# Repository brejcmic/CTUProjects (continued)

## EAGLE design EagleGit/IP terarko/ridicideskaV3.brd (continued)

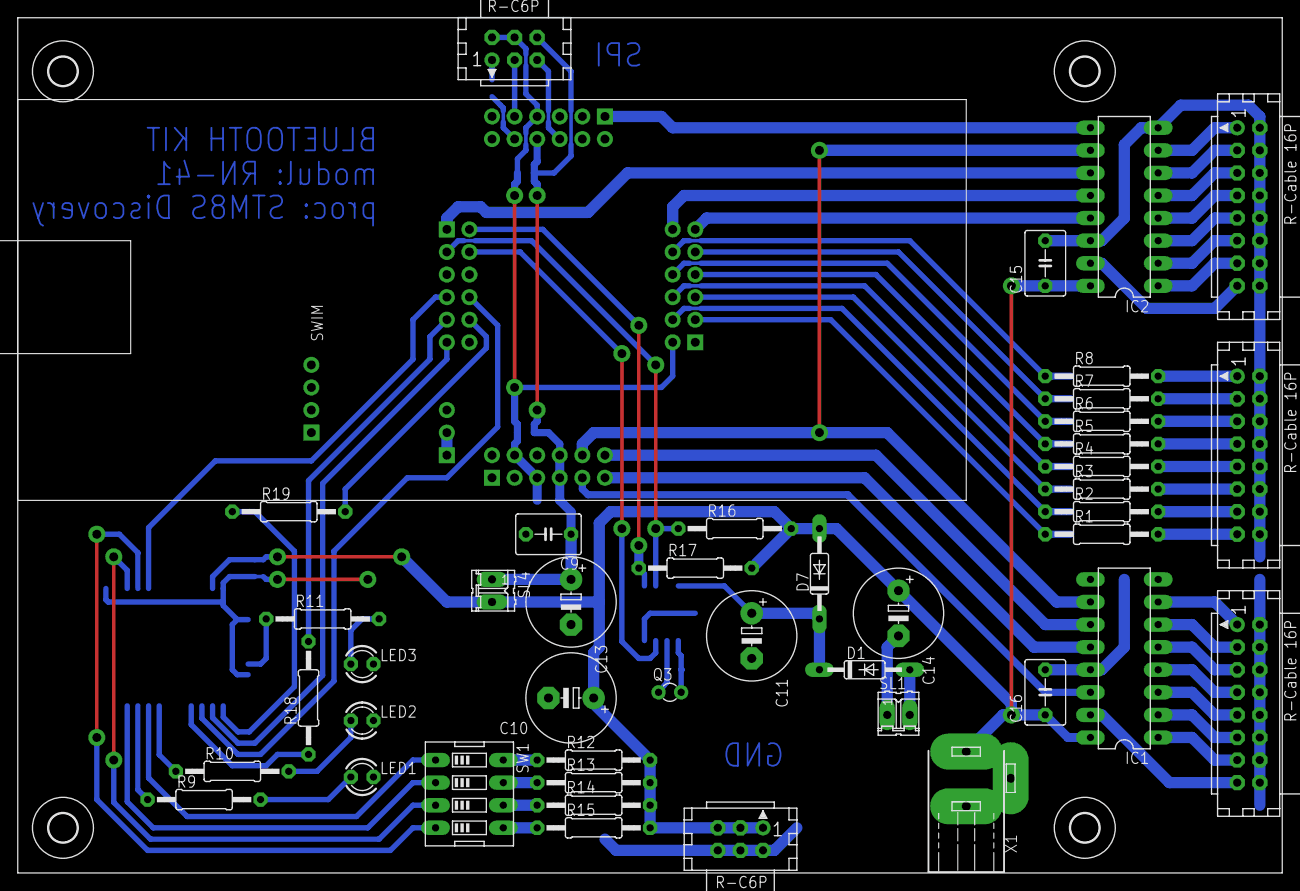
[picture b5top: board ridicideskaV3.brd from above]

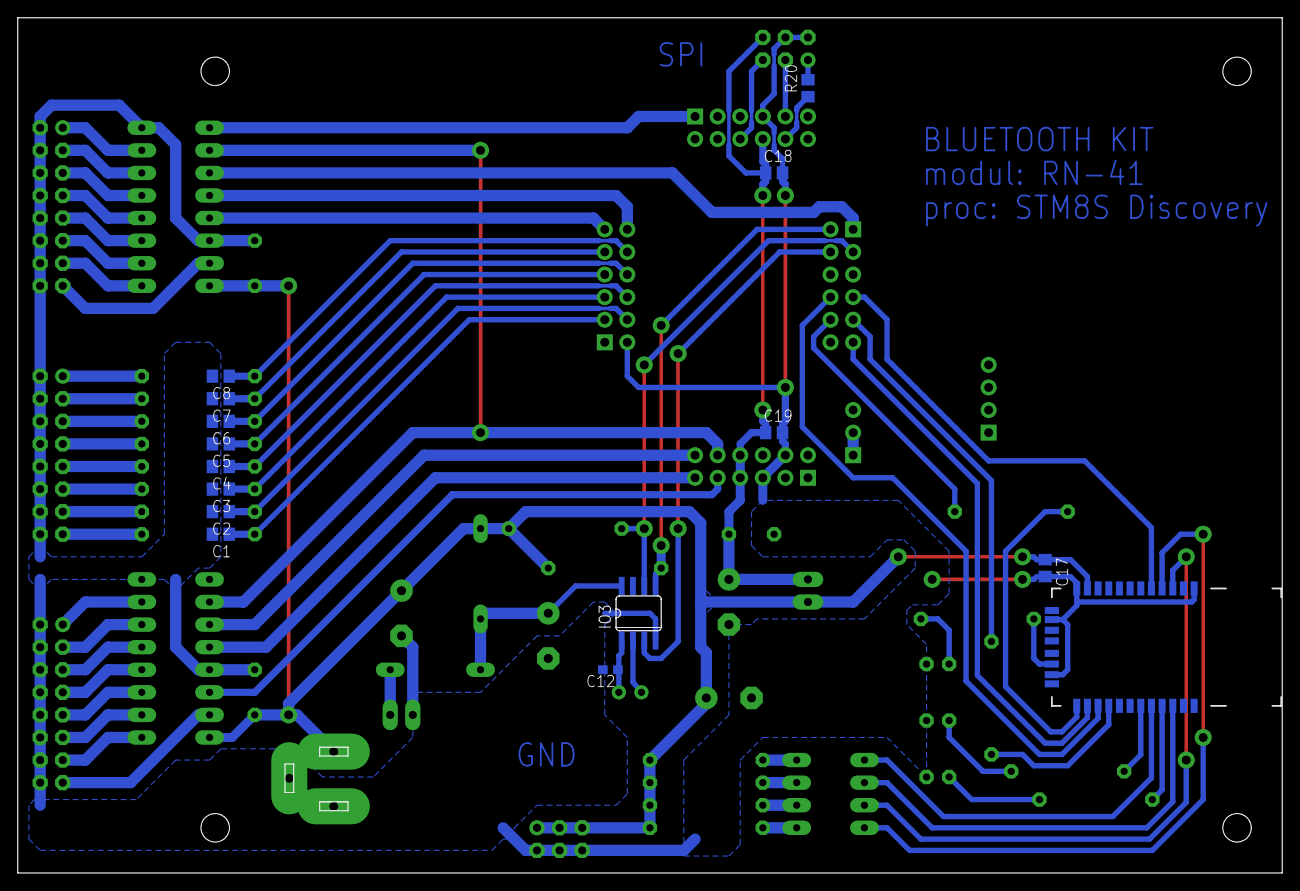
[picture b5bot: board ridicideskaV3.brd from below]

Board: 2 copper layers, 142.2 x 96.2 mm, 63 parts (15 on the bottom side), 76 nets.

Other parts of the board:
U$2, U$3, U$4, U$5: 3,2
